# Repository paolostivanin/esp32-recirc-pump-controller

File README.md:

# ESP32 pump controller for Grundfos Comfort AutoAdapt recirculating hot water pump

This project contains a KiCad project for a replacement controller board that I
built for a Grundfos Comfort AutoAdapt recirculating hot water pump using an
ESP32-C3-MINI-1 board. This allows the pump to be controlled remotely, and
integrated in to Home Assistant using [ESPHome][esphome].  There's some more information 
on this in the [Home Assistant community forum](https://community.home-assistant.io/t/hacking-a-grundfos-comfort-autoadapt-recirculating-hot-water-pump-for-esphome/684475).

The AutoAdapt pump is supposed to predict when you need hot water based on
previous usage patterns, but it never worked reliably for me. I originally
planned to put the pump into "always on" mode and use an external relay to
control it from Home Assistant, but unfortunately, every time you cut the power
to the pump, it reverts to AutoAdapt mode. I originally started
reverse-engineering the pump to figure out if it was possible to force it to be
always on (you can quite easily) but then got a bit carried away with a better
solution.

_Obvious warnings: copy this at your own risk. The board was designed based on
reverse engineering of the original board, so it's quite possible that I missed
some important safety considerations when doing so. The pump is mains powered,
so disconnect it before disassembly, and be aware that capacitors on the the
power supply board may still hold charge. If you don't understand what this
means, stop now._

## Original control board

The pump contains 3 PCBs. The front board is the control board. The middle
board is the power supply, and the rear board is the motor driver.

The modular design of the PCBs makes it quite easy to swap in a different
control board that re-uses the existing power supply and motor driver boards.

The power supply board provides 14V to the other two boards. The motor board
provides a 5V supply which is used by the microcontrollers on both the motor 
board and the control board.

The control board connects to the power supply board via a six pin connector
with the following pins (facing the control board connector):

```
+---------+---------+---------+
|  Temp   |   5V    |    0V   |
+---------+---------+---------+
|  Motor  |   ??    |   14V   |
+---------+---------+---------+
```

The original controller uses a PIC18F14K50 microcontroller.

The motor control appears to be an active-high, open-drain arrangement, meaning that the
controller pulls it to ground to turn the motor off, and lets it float (pulled up by PSU board) to 
turn it on. This means that if you simply remove the control board, the pump will
run all the time. The circuit on the motor controller looks like this may actually be treated 
as an analog input, possibly allowing control of motor speed.

I'm unsure of the details of the pump temperature sensor, beyond that it gives an
analog signal that varies with the temperature of the pump.  The replacement
board feeds it into a potential divider to ensure that it remains < 3.3V, and I
then calibrated it empirically. This is used to measure the temperature of
water flowing out of the tank.

The `??` pin is connected to the analog ground reference voltage input (AVss)
on the microcontroller (30F2010) on the motor driver board. It's connected to ground
on the controller board, but appears to be pulled up to 5V by the PSU board.  I
don't understand this arrangement. The replacement board just connects it to ground
as per the original.

The other input to the board is from an external temperature sensor used to
measure the temperature of returning water. This is a simple 10K NTC, and
connects via 2 pins on a 4 pin header.

### Pump variants

This pump is sold in a few different variants with different controllers. My
guess is that these are identical internally except for the front control board
and face plate. The advantage of the "AutoAdapt" variant is that it has the
external return temperature sensor.

## Disassembly

The front of the pump is held on by four clips, and can be removed by carefully
levering behind the face plate around the circumference of the pump.  

The external temperature sensor is coiled around the face plate, and is also just
clipped on. Once removed, it can be unplugged from the board (I think there may
have been a spot of glue originally), and then the original PCB can be removed - it's 
held in by 4 clips which need to be gently bent back.

At this point, the power supply board can also be removed by pulling on it, but
you don't need to.

The motor driver PCB is hidden under a plastic cover that is _extremely_ hard
to remove, but you definitely don't need to.

## ESP32 control board

The replacement board uses an ESP32-C3-MINI-1 module. It has its own buck
regulator supply to drop the 14V input to 3.3V, as the 5V linear regulator
supply from the motor controller is almost certainly insufficient for the
ESP32.

The power supply uses an AP63203, and can be populated using the components
from a [SparkFun BabyBuck Regulator Breakout Board](https://thepihut.com/products/sparkfun-babybuck-regulator-breakout-3-3v-ap63203).

The other parts of the board are:

### Motor driver

This uses an AO3400A MOSFET, and has a 680R series resistor because that's what
the original board had.

### Pump temperature input

This uses a potential divider to ensure that the input signal from the 5V
driver board remains less than 3.3V.

### Return temperature input

This uses a 10K resistor to form a potential divider.

### Switch input

The front panel switch pulls this to ground. The switch is a 2x3mm SMD tactile
switch.  I used a [CUI TS19-32-06-BK-70-1-SMT-TR-67](https://www.lcsc.com/datasheet/lcsc_datasheet_2312270104_CUI-TS19-32-06-BK-70-1-SMT-TR-67_C6723741.pdf).

### LED outputs

There are five LEDs on the front panel:

* Thermometer logo
* "Auto-adapt" logo (2 LEDs)
* "100%" logo
* "Sensor" logo

These are 0603 size LEDs.

I made the first four blue, and the last one red, and all have suitable
current-limiting resistors (0402).

### Connectors

The six pin connector for the power supply is an almost-standard 2x3 2.54mm
female header, but it's taller than normal. Obviously you could steal the
connector from the old board, but I wanted to keep the old one intact. I
managed to find some headers with extra long pins, and added some spacers taken
from other header pins.

The temperature connector is a standard 2x2 right angle 2.54mm pin header.

The board has holes for exposing the ESP32 UART and power, but I've not used
these. There may not be enough clearance between the back of the board and the
front panel if you fit these.

## Board revisions

I made a mistake in the design and connected the pump temperature input to
GPIO5/ADC2 which is apparently incompatible with enabling wifi on the ESP32-C3.
I fixed this by swapping GPIO4 and GPIO5 with jumper wires, and have updated
the PCB design in this repo to match, but this does mean that the PCB in this
repository has technically never been built or tested.

## Board fabrication / assembly

I got my boards made by PCBWay, and assembled them myself. Most resistors and
diodes are 0402 because I have lots of these already, but there's space to make
them bigger.

If hand-soldering 0402 components is not your idea of fun, you could probably
get the front of the board assembled by PCBWay / JLCPCB, leaving just the LEDs,
resistors and switch to do on the back, and the connectors.  You could fairly
easily increase the size of the resistors to make soldering easier.

## ESPHome

My ESPHome configuration is available [here](esphome/pump-controller.yaml).

## Schematic

[esphome]: https://esphome.io

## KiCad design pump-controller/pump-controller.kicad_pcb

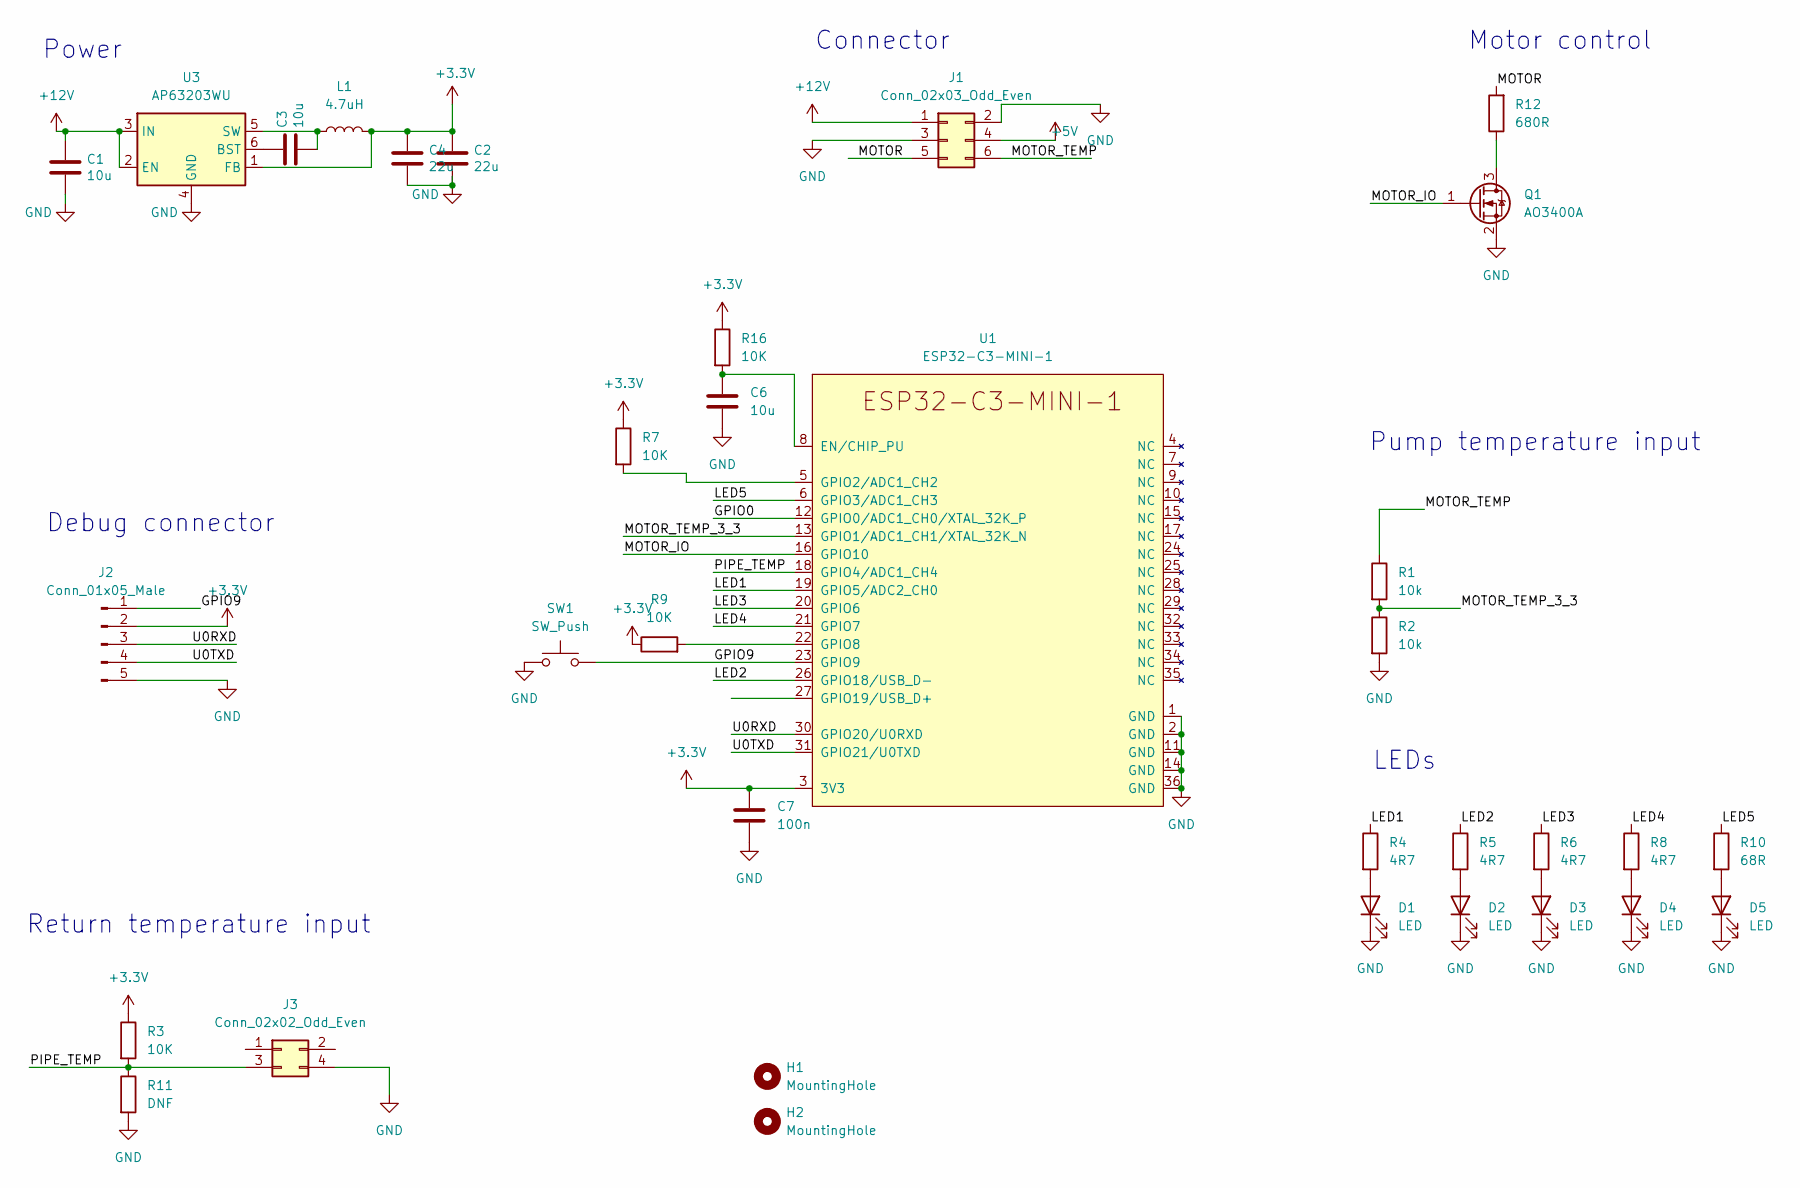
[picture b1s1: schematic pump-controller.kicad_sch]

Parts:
C1: 10u; C_1206_3216Metric
C2, C4: 22u; C_0805_2012Metric
C3, C6: 10u; C_0402_1005Metric
C7: 100n; C_0402_1005Metric
D1, D2, D3, D4, D5: LED; LED_0603_1608Metric
H1, H2: MountingHole; MountingHole_4mm
J1: Conn_02x03_Odd_Even; PinSocket_2x03_P2.54mm_Vertical
J2: Conn_01x05_Male; PinHeader_1x05_P2.54mm_Vertical
J3: Conn_02x02_Odd_Even; PinHeader_2x02_P2.54mm_Horizontal
L1: 4.7uH; L_Abracon_ASPI-4030S
Q1: AO3400A; SOT-23
R1, R2: 10k; R_0402_1005Metric
R3, R7, R9, R16: 10K; R_0402_1005Metric
R4, R5, R6, R8: 4R7; R_0402_1005Metric
R10: 68R; R_0402_1005Metric
R11: DNF; R_0402_1005Metric
R12: 680R; R_0402_1005Metric
SW1: SW_Push; SW_SPST_3.5x2.0
U1: ESP32-C3-MINI-1
U3: AP63203WU; TSOT-23-6

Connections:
+3.3V: C2.1, C4.1, C7.1, J2.2, L1.2, R3.1, R7.1, R9.1, R16.1, U1.3 (3V3), U3.1 (FB)
+5V: J1.4
+12V: C1.1, J1.1, U3.2 (EN), U3.3 (IN)
/GPIO0: U1.12 (GPIO0/ADC1_CH0/XTAL_32K_P)
/GPIO9: J2.1, SW1.2, U1.23 (GPIO9)
/LED1: R4.1, U1.19 (GPIO5/ADC2_CH0)
/LED2: R5.1, U1.26 (GPIO18/USB_D-)
/LED3: R6.1, U1.20 (GPIO6)
/LED4: R8.1, U1.21 (GPIO7)
/LED5: R10.1, U1.6 (GPIO3/ADC1_CH3)
/MOTOR: J1.5, R12.2
/MOTOR_IO: Q1.1 (G), U1.16 (GPIO10)
/MOTOR_TEMP: J1.6, R1.1
/MOTOR_TEMP_3_3: R1.2, R2.1, U1.13 (GPIO1/ADC1_CH1/XTAL_32K_N)
/PIPE_TEMP: J3.3, R3.2, R11.1, U1.18 (GPIO4/ADC1_CH4)
/U0RXD: J2.3, U1.30 (GPIO20/U0RXD)
/U0TXD: J2.4, U1.31 (GPIO21/U0TXD)
GND: C1.2, C2.2, C4.2, C6.2, C7.2, D1.1 (K), D2.1 (K), D3.1 (K), D4.1 (K), D5.1 (K), J1.2, J1.3, J2.5, J3.4, Q1.2 (S), R2.2, R11.2, SW1.1, U1.1 (GND), U1.2 (GND), U1.11 (GND), U1.14 (GND), U1.36 (GND), U3.4 (GND)
unnamed: D1.2 (A), R4.2
unnamed: D2.2 (A), R5.2
unnamed: D3.2 (A), R6.2
unnamed: D4.2 (A), R8.2
unnamed: D5.2 (A), R10.2
unnamed: Q1.3 (D), R12.1
unnamed: C6.1, R16.2, U1.8 (EN/CHIP_PU)
unnamed: R7.2, U1.5 (GPIO2/ADC1_CH2)
unnamed: R9.2, U1.22 (GPIO8)
unnamed: C3.1, U3.6 (BST)
unnamed: C3.2, L1.1, U3.5 (SW)

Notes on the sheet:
LEDs
Power
Pump temperature input
Debug connector
Return temperature input
Motor control
Connector

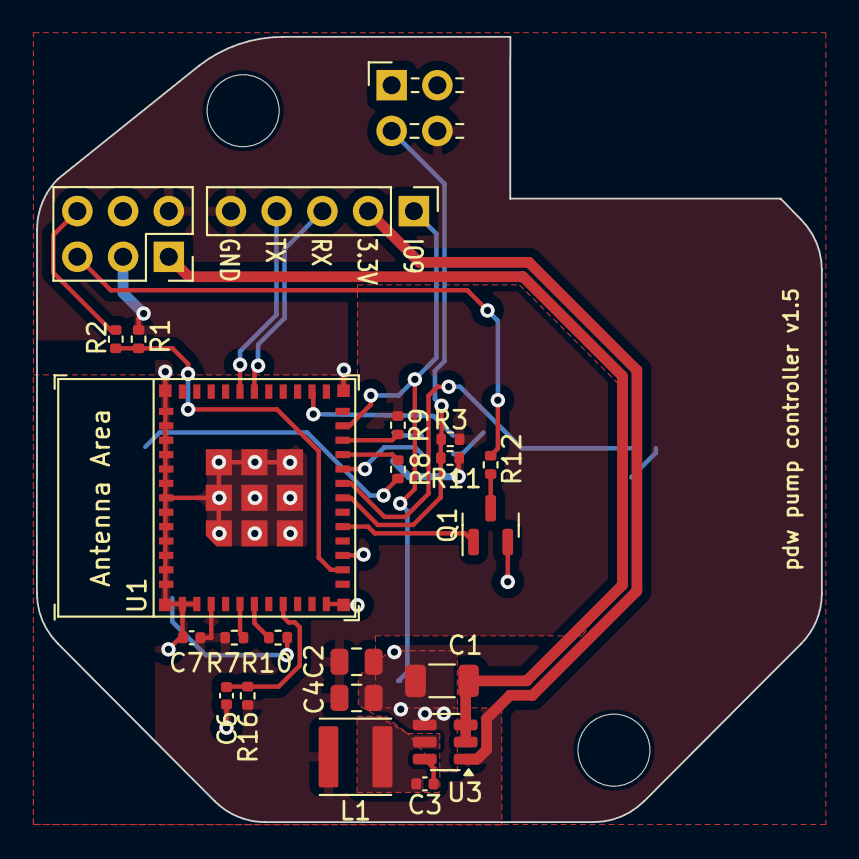
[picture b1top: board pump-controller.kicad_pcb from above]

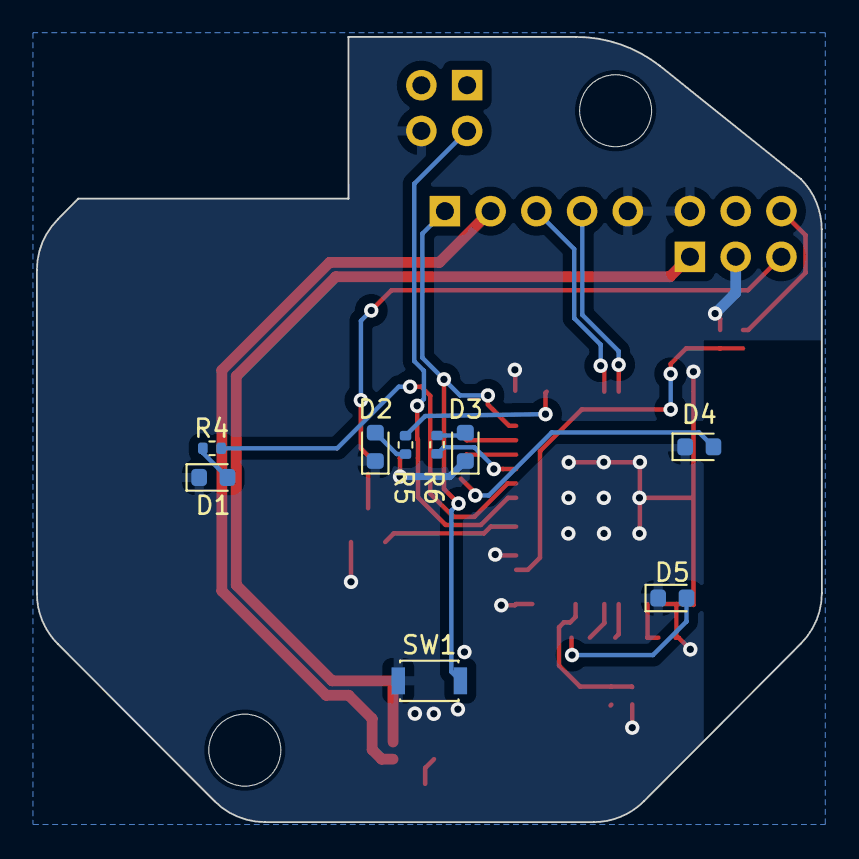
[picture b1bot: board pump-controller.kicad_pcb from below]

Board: 2 copper layers, 43.6 x 43.6 mm, 34 parts (9 on the bottom side), 27 nets.

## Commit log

2024-12-24 Initial commit.
2024-12-24 Fix image link
2024-12-24 Crop image.
2024-12-24 More images.
2024-12-24 Minor fix
2024-12-24 KiCad project
2024-12-24 Add ESPHome config.
2024-12-24 Move esphome config.
2025-03-05 Trivial tweaks, added version number.
2025-03-21 KiCad save.
2025-03-21 Add missing mounting holes, tweak capacitor footprints.
2025-09-26 pump-controller: add legionella timer and improve control logic
    Changes:
    - Added 5-minute legionella_timer script to force pump circulation
    after boiler anti-legionella cycle, ensuring 65 °C water flushes
    through all pipes.
    - Integrated legionella timer into pump control logic (update).
    - Exposed legionella_timer_remaining sensor for HA monitoring.
2025-09-26 pump-controller: refine thermometer LED behavior
    Changes:
    - LED1 (thermometer logo) now reflects pump status more clearly:
    * OFF when pump is OFF.
    * Flashing when pump just turned ON due to ΔT > 15 °C.
    * Solid ON when pump is running for other reasons (manual, boost, legionella, or stable ΔT).
    - Removed confusing case where LED1 could remain ON even if the pump was OFF.
2025-09-26 pump-controller: extend physical button to trigger boost or legionella cycles
    Changes:
    - Updated GPIO button handler:
    * Short press (<1s) → start 30-minute Boost cycle.
    * Long press (≥3s) → start 5-minute Legionella flush.
    - Keeps existing HA entity ("Button") for diagnostics.
    Why:
2025-09-29 Change switch, update zones.
2025-10-01 esp32: refactor pump controller
    - add MQTT auth + availability (online/offline) with HA discovery
    - add HA-configurable ΔT thresholds (number.delta_on / number.delta_off)
    - expose Legionella flush as HA button
    - enforce Boost/Legionella exclusivity
    - change LED1 from flash -> pulse for smoother UX
    - unify timer units to minutes
2025-10-01 docs: update README to v3 with clearer entities and MQTT topics
    - Rewrite README to version 3:
    * Clarify ΔT definition (Flow − Return)
    * Show exact HA entity IDs and friendly names
    * Add ΔT Flow-Pump sensor in entity table
    * Separate MQTT topics into published vs subscribed
    * Improve LED behavior section wording
2025-10-20 Update to v3.3
    - Added symmetric ΔT updates (both flow/return sensors)
    - Added MQTT events topic section
    - Added logger DEBUG configuration example
    - Minor wording and LED pulse clarification
2025-10-20 pump-controller: resume timers and restore switch state on reboot
    - Added robust on_boot resume logic:
    • Detects active Boost or Legionella timers after reboot.
    • Restarts countdown tickers and restores corresponding LEDs.
    • Publishes MQTT "resumed" events for HA visibility.
    • Forces update_pump_state to keep pump logic in sync.
    - Added `restore_mode: RESTORE_DEFAULT_OFF` to:
2025-10-22 Revert to previous switch.
2025-11-24 v4.0 use HA api and not mqtt
2025-11-24 Add credits
2025-11-24 Revise acknowledgments in README.md
2025-12-15 Update code and readme
